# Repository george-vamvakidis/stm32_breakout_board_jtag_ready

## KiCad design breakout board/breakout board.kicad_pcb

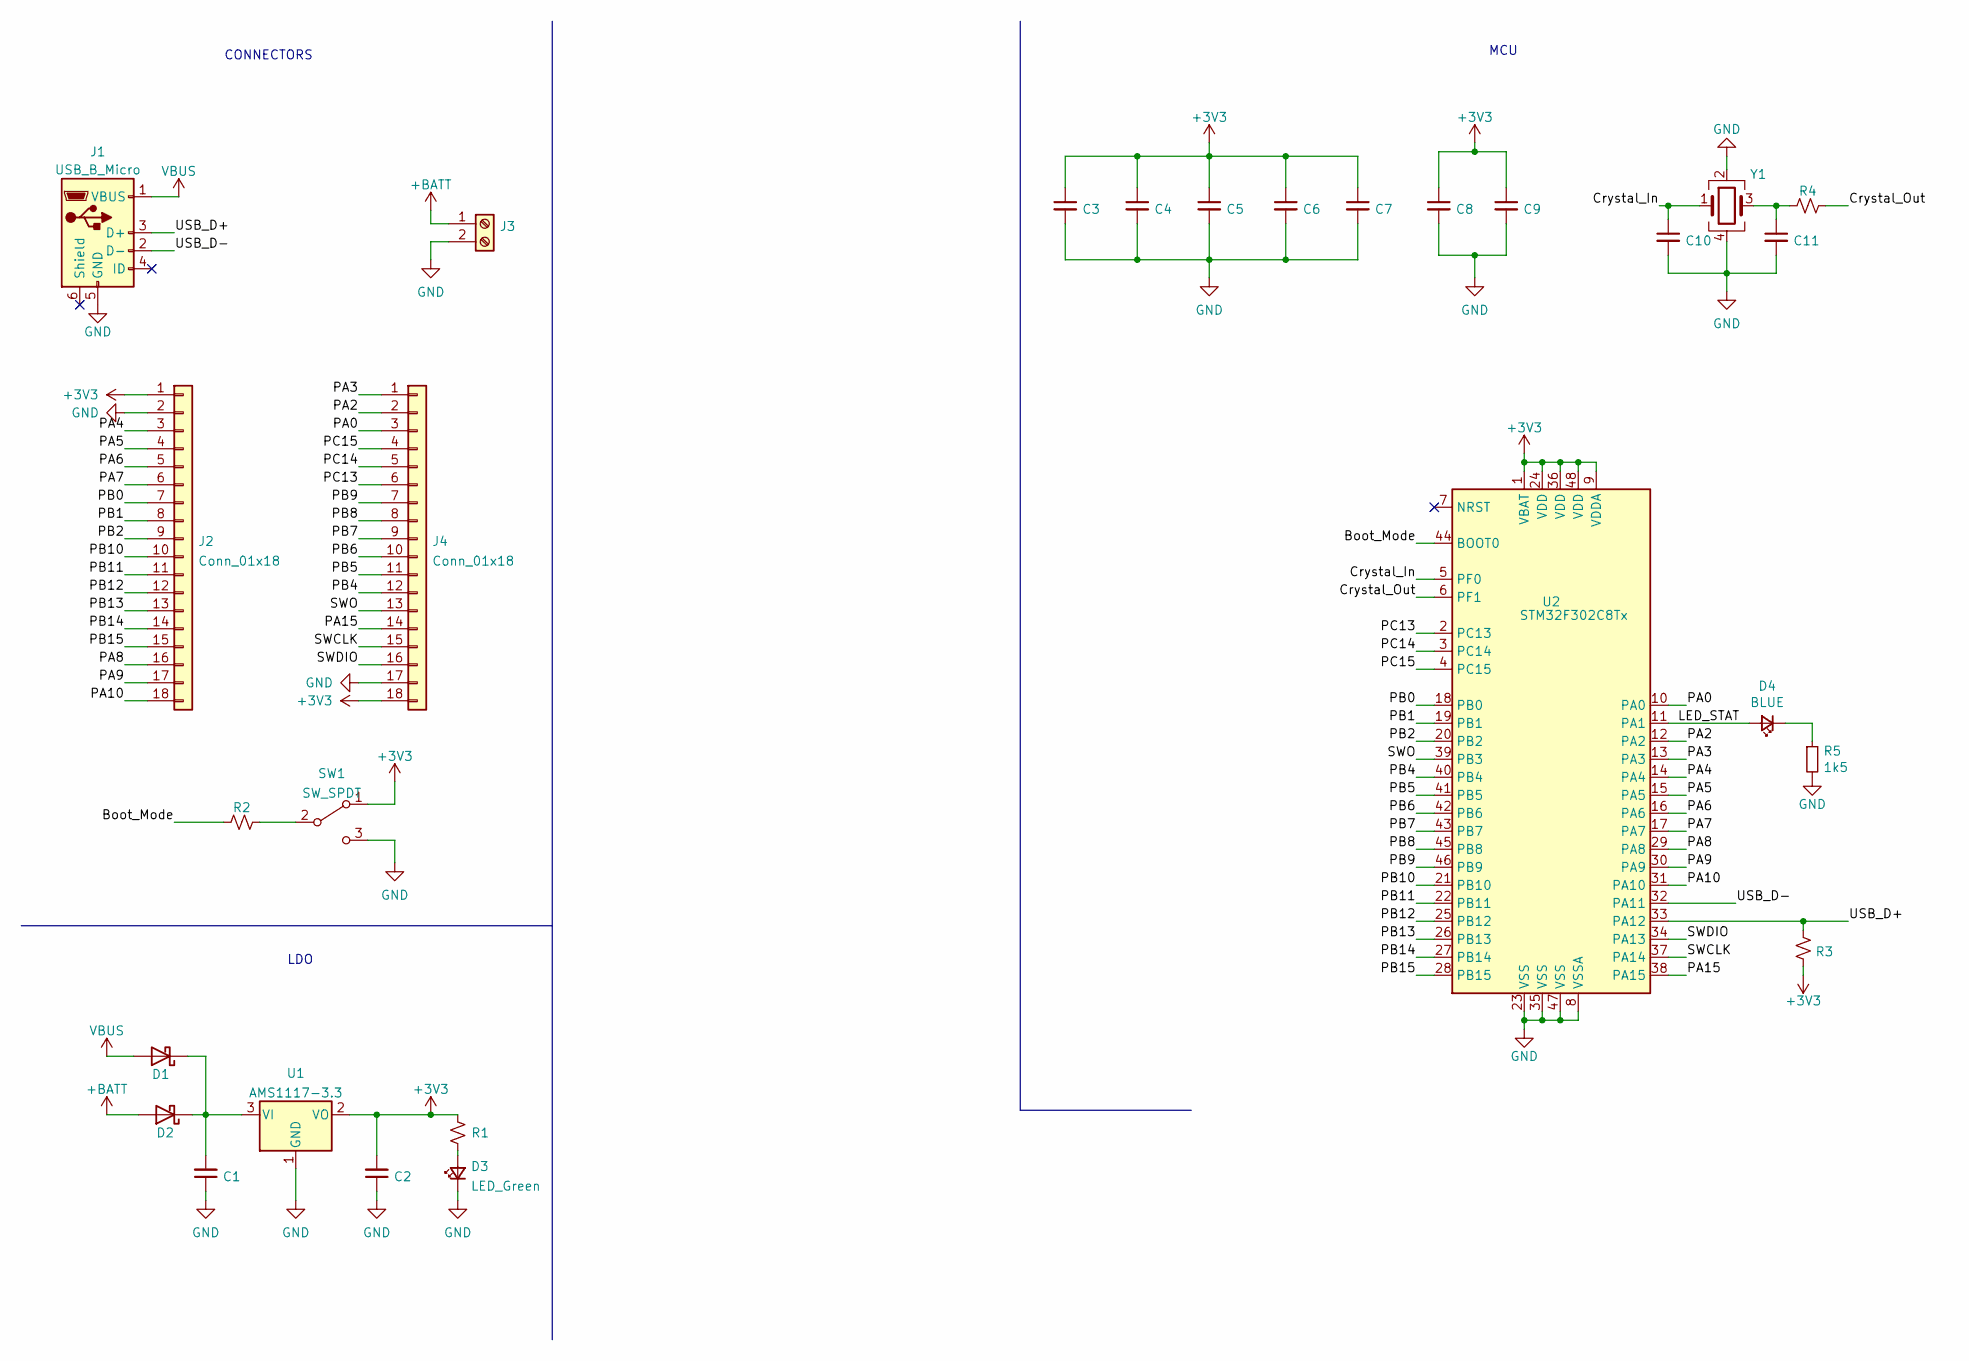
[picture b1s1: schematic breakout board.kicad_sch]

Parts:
C1, C2: 10uF; C_0603_1608Metric
C3, C4, C5, C6, C8: 100nF; C_0402_1005Metric
C7: 4.7uF; C_0603_1608Metric
C9: 1uF; C_0603_1608Metric
C10, C11: 12pF; C_0402_1005Metric
D1, D2: 1N5819; D_SOD-123
D3: LED_Green; LED_1210_3225Metric
D4: BLUE; LED_0603_1608Metric; LCSC Part # C72041
J1: USB_B_Micro; USB_Micro-B_Wuerth_629105150521
J2, J4: Conn_01x18; PinSocket_1x18_P2.54mm_Vertical
J3: Screw_Terminal_01x02; TerminalBlock_Altech_AK300-2_P5.00mm
R1: 330; R_0603_1608Metric
R2: 10k; R_0603_1608Metric
R3: 1.5k; R_0603_1608Metric
R4: 47; R_0603_1608Metric
R5: 1k5; R_0603_1608Metric; LCSC Part # C22843
SW1: SW_SPDT; PinHeader_1x03_P2.54mm_Vertical_SMD_Pin1Left
U1: AMS1117-3.3; SOT-223-3_TabPin2
U2: STM32F302C8Tx; LQFP-48_7x7mm_P0.5mm
Y1: X322516MLB4SI; Crystal_SMD_3225-4Pin_3.2x2.5mm

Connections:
+3V3: C2.2, C3.1, C4.1, C5.1, C6.1, C7.1, C8.1, C9.1, J2.1, J4.18, R1.2, R3.2, SW1.1 (A), U1.2 (VO), U2.1 (VBAT), U2.9 (VDDA), U2.24 (VDD), U2.36 (VDD), U2.48 (VDD)
+BATT: D2.2 (A), J3.1
/Boot_Mode: R2.1, U2.44 (BOOT0)
/Crystal_In: C10.1, U2.5 (PF0), Y1.1
/Crystal_Out: R4.2, U2.6 (PF1)
/LED_STAT: D4.2 (A), U2.11 (PA1)
/PA0: J4.3, U2.10 (PA0)
/PA2: J4.2, U2.12 (PA2)
/PA3: J4.1, U2.13 (PA3)
/PA4: J2.3, U2.14 (PA4)
/PA5: J2.4, U2.15 (PA5)
/PA6: J2.5, U2.16 (PA6)
/PA7: J2.6, U2.17 (PA7)
/PA8: J2.16, U2.29 (PA8)
/PA9: J2.17, U2.30 (PA9)
/PA10: J2.18, U2.31 (PA10)
/PA15: J4.14, U2.38 (PA15)
/PB0: J2.7, U2.18 (PB0)
/PB1: J2.8, U2.19 (PB1)
/PB2: J2.9, U2.20 (PB2)
/PB4: J4.12, U2.40 (PB4)
/PB5: J4.11, U2.41 (PB5)
/PB6: J4.10, U2.42 (PB6)
/PB7: J4.9, U2.43 (PB7)
/PB8: J4.8, U2.45 (PB8)
/PB9: J4.7, U2.46 (PB9)
/PB10: J2.10, U2.21 (PB10)
/PB11: J2.11, U2.22 (PB11)
/PB12: J2.12, U2.25 (PB12)
/PB13: J2.13, U2.26 (PB13)
/PB14: J2.14, U2.27 (PB14)
/PB15: J2.15, U2.28 (PB15)
/PC13: J4.6, U2.2 (PC13)
/PC14: J4.5, U2.3 (PC14)
/PC15: J4.4, U2.4 (PC15)
/SWCLK: J4.15, U2.37 (PA14)
/SWDIO: J4.16, U2.34 (PA13)
/SWO: J4.13, U2.39 (PB3)
/USB_D+: J1.3 (D+), R3.1, U2.33 (PA12)
/USB_D-: J1.2 (D-), U2.32 (PA11)
GND: C1.1, C2.1, C3.2, C4.2, C5.2, C6.2, C7.2, C8.2, C9.2, C10.2, C11.2, D3.1 (K), J1.5 (GND), J2.2, J3.2, J4.17, R5.2, SW1.3 (C), U1.1 (GND), U2.8 (VSSA), U2.23 (VSS), U2.35 (VSS), U2.47 (VSS), Y1.2, Y1.4
unnamed: C1.2, D1.1 (K), D2.1 (K), U1.3 (VI)
unnamed: C11.1, R4.1, Y1.3
unnamed: D3.2 (A), R1.1
unnamed: D4.1 (K), R5.1
unnamed: R2.2, SW1.2 (B)
VBUS: D1.2 (A), J1.1 (VBUS)

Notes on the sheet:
LDO
MCU
CONNECTORS

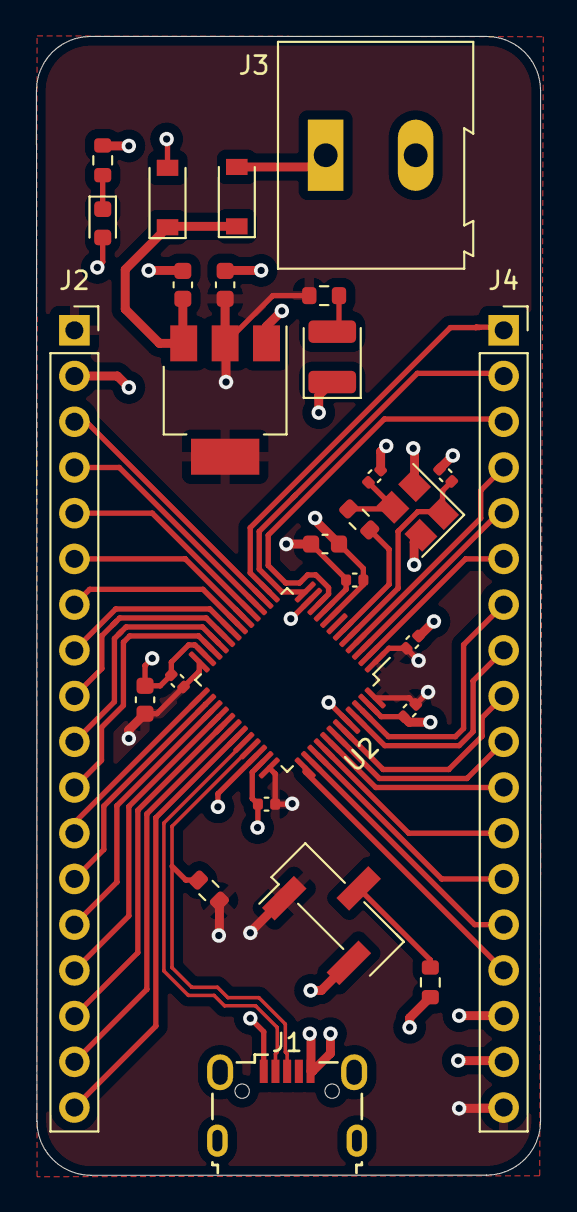
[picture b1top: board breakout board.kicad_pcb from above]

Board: 4 copper layers, 28.0 x 63.3 mm, 28 parts (0 on the bottom side), 47 nets.
